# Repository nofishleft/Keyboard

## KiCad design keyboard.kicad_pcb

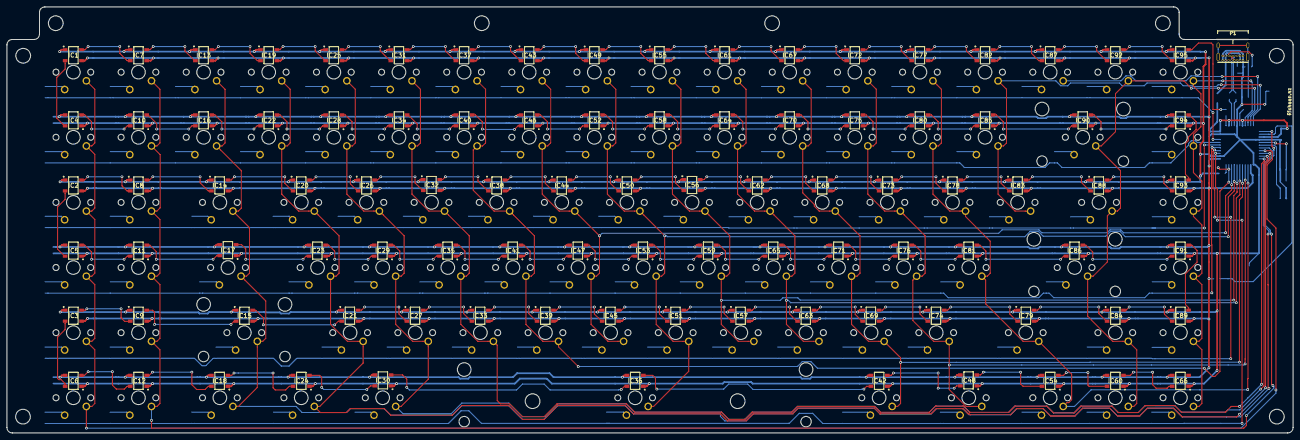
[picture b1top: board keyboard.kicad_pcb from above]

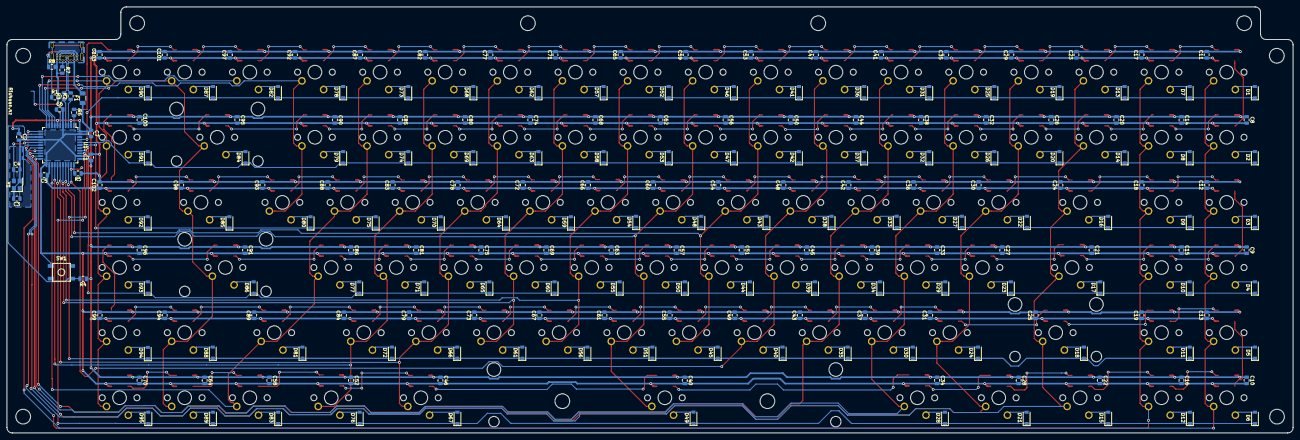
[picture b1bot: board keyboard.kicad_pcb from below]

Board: 2 copper layers, 376.2 x 124.6 mm, 400 parts (209 on the bottom side), 230 nets.

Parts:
C1, C2, C5: 0.1uF; C_0805_2012Metric
C3, C4: 22pF; C_0805_2012Metric
C6: 1uF; C_0805_2012Metric
C7: 10uF; C_0805_2012Metric
C8, C9, C10, C11, C12, C13, C14, C15, C16, C17, C18, C19, C20, C21, C22, C23, C24, C25, C26, C27, C28, C29, C30, C31, C32, C33, C34, C35, C36, C37, C38, C39, C40, C41, C42, C43, C44, C45, C46, C47, C48, C49, C50, C51, C52, C53, C54, C55, C56, C57, C58, C59, C60, C61, C62, C63, C64, C65, C66, C67, C68, C69, C70, C71, C72, C73, C74, C75, C77, C78, C79, C80, C81, C82, C83, C84, C85, C86, C87, C88, C89, C90, C91, C92, C93, C94, C95, C96, C97, C98, C99, C100, C101, C102, C103: 100nF; C_0805_2012Metric
D1, D2, D3, D4, D5, D6, D7, D8, D9, D10, D11, D12, D13, D14, D15, D16, D17, D18, D19, D20, D21, D22, D23, D24, D25, D26, D27, D28, D29, D30, D31, D32, D33, D34, D35, D36, D37, D38, D39, D40, D41, D42, D43, D44, D45, D46, D47, D48, D49, D50, D51, D52, D53, D54, D55, D56, D57, D58, D59, D60, D61, D62, D63, D64, D65, D66, D67, D68, D69, D70, D71, D72, D73, D74, D75, D76, D77, D78, D79, D80, D81, D82, D83, D84, D85, D86, D87, D88, D89, D90, D91, D92, D93, D94, D95: SOD-123; D_SOD-123
F1: 500mA; Fuse_1206_3216Metric
IC1, IC2, IC3, IC4, IC5, IC6, IC7, IC8, IC9, IC10, IC11, IC12, IC13, IC14, IC15, IC16, IC17, IC18, IC19, IC20, IC21, IC22, IC23, IC24, IC25, IC26, IC27, IC28, IC29, IC30, IC31, IC32, IC33, IC34, IC35, IC36, IC37, IC38, IC39, IC40, IC41, IC42, IC43, IC44, IC45, IC46, IC47, IC48, IC49, IC50, IC51, IC52, IC53, IC54, IC55, IC56, IC57, IC58, IC59, IC60, IC61, IC62, IC63, IC64, IC65, IC66, IC67, IC68, IC69, IC70, IC71, IC72, IC73, IC74, IC75, IC76, IC77, IC78, IC79, IC80, IC81, IC82, IC83, IC84, IC85, IC86, IC87, IC88, IC89, IC90, IC91, IC92, IC93, IC94, IC95: WS2812B
MX0-0, MX0-1, MX0-2, MX0-3, MX0-4, MX0-5, MX0-6, MX0-7, MX0-8, MX0-9, MX0-10, MX0-11, MX0-12, MX0-13, MX0-14, MX0-15, MX0-16, MX0-17, MX1-0, MX1-1, MX1-2, MX1-3, MX1-4, MX1-5, MX1-6, MX1-7, MX1-8, MX1-9, MX1-10, MX1-11, MX1-12, MX1-13, MX1-14, MX1-17, MX2-0, MX2-1, MX2-3, MX2-4, MX2-5, MX2-6, MX2-7, MX2-8, MX2-9, MX2-10, MX2-11, MX2-12, MX2-13, MX2-14, MX2-17, MX3-0, MX3-1, MX3-3, MX3-4, MX3-5, MX3-6, MX3-7, MX3-8, MX3-9, MX3-10, MX3-11, MX3-12, MX3-13, MX3-17, MX4-0, MX4-1, MX4-3, MX4-4, MX4-5, MX4-6, MX4-7, MX4-8, MX4-9, MX4-10, MX4-11, MX4-12, MX4-16, MX4-17, MX5-0, MX5-1, MX5-3, MX5-13, MX5-16, MX5-17: MX-NoLED; MXOnly-1U-NoLED
MX1-16: MX-NoLED; MXOnly-2U-NoLED
MX2-2, MX2-16, MX5-2, MX5-4, MX5-12: MX-NoLED; MXOnly-1.5U-NoLED
MX3-2, MX4-13: MX-NoLED; MXOnly-1.75U-NoLED
MX3-16, MX4-2: MX-NoLED; MXOnly-2.25U-NoLED
MX5-8: MX-NoLED; MXOnly-6.25U-NoLED
MX5-11: MX-NoLED; MXOnly-1.25U-NoLED
P1: USB_C_Plug_USB2.0; USB_C_GCT_USB4085
R1: 33k; R_0805_2012Metric
R2, R3: 22; R_0805_2012Metric
R4, R5: 10k; R_0805_2012Metric
R6: 500; R_0805_2012Metric
R7, R8: 5.1k; R_0805_2012Metric
SW1: SW_Push; SKQG-1155865
U1: ATmega32U4-AU; TQFP-44_10x10mm_P0.8mm
Y1: 16MHz; Crystal_SMD_3225-4Pin_3.2x2.5mm

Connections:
+5V: C1.1, C2.1, C5.1, C7.1, C8.1, C9.1, C10.1, C11.1, C12.1, C13.1, C14.1, C15.1, C16.1, C17.1, C18.1, C19.1, C20.1, C21.1, C22.1, C23.1, C24.1, C25.1, C26.1, C27.1, C28.1, C29.1, C30.1, C31.1, C32.1, C33.1, C34.1, C35.1, C36.1, C37.1, C38.1, C39.1, C40.1, C41.1, C42.1, C43.1, C44.1, C45.1, C46.1, C47.1, C48.1, C49.1, C50.1, C51.1, C52.1, C53.1, C54.1, C55.1, C56.1, C57.1, C58.1, C59.1, C60.1, C61.1, C62.1, C63.1, C64.1, C65.1, C66.1, C67.1, C68.1, C69.1, C70.1, C71.1, C72.1, C73.1, C74.1, C75.1, C77.1, C78.1, C79.1, C80.1, C81.1, C82.1, C83.1, C84.1, C85.1, C86.1, C87.1, C88.1, C89.1, C90.1, C91.1, C92.1, C93.1, C94.1, C95.1, C96.1, C97.1, C98.1, C99.1, C100.1, C101.1, C102.1, C103.1, F1.1, IC1.3, IC2.3, IC3.3, IC4.3, IC5.3, IC6.3, IC7.3, IC8.3, IC9.3, IC10.3, IC11.3, IC12.3, IC13.3, IC14.3, IC15.3, IC16.3, IC17.3, IC18.3, IC19.3, IC20.3, IC21.3, IC22.3, IC23.3, IC24.3, IC25.3, IC26.3, IC27.3, IC28.3, IC29.3, IC30.3, IC31.3, IC32.3, IC33.3, IC34.3, IC35.3, IC36.3, IC37.3, IC38.3, IC39.3, IC40.3, IC41.3, IC42.3, IC43.3, IC44.3, IC45.3, IC46.3, IC47.3, IC48.3, IC49.3, IC50.3, IC51.3, IC52.3, IC53.3, IC54.3, IC55.3, IC56.3, IC57.3, IC58.3, IC59.3, IC60.3, IC61.3, IC62.3, IC63.3, IC64.3, IC65.3, IC66.3, IC67.3, IC68.3, IC69.3, IC70.3, IC71.3, IC72.3, IC73.3, IC74.3, IC75.3, IC76.3, IC77.3, IC78.3, IC79.3, IC80.3, IC81.3, IC82.3, IC83.3, IC84.3, IC85.3, IC86.3, IC87.3, IC88.3, IC89.3, IC90.3, IC91.3, IC92.3, IC93.3, IC94.3, IC95.3, R4.1, U1.2, U1.7, U1.14, U1.24, U1.34, U1.44
COL0: MX0-0.1, MX1-0.1, MX2-0.1, MX3-0.1, MX4-0.1, MX5-0.1, U1.19
COL1: MX0-1.1, MX1-1.1, MX2-1.1, MX3-1.1, MX4-1.1, MX5-1.1, U1.12
COL2: MX0-2.1, MX1-2.1, MX2-2.1, MX3-2.1, MX4-2.1, MX5-2.1, U1.18
COL3: MX0-3.1, MX1-3.1, MX2-3.1, MX3-3.1, MX4-3.1, MX5-3.1, U1.20
COL4: MX0-4.1, MX1-4.1, MX2-4.1, MX3-4.1, MX4-4.1, MX5-4.1, U1.21
COL5: MX0-5.1, MX1-5.1, MX2-5.1, MX3-5.1, MX4-5.1, U1.22
COL6: MX0-6.1, MX1-6.1, MX2-6.1, MX3-6.1, MX4-6.1, U1.32
COL7: MX0-7.1, MX1-7.1, MX2-7.1, MX3-7.1, MX4-7.1, U1.31
COL8: MX0-8.1, MX1-8.1, MX2-8.1, MX3-8.1, MX4-8.1, MX5-8.1, U1.30
COL9: MX0-9.1, MX1-9.1, MX2-9.1, MX3-9.1, MX4-9.1, U1.29
COL10: MX0-10.1, MX1-10.1, MX2-10.1, MX3-10.1, MX4-10.1, U1.28
COL11: MX0-11.1, MX1-11.1, MX2-11.1, MX3-11.1, MX4-11.1, MX5-11.1, U1.27
COL12: MX0-12.1, MX1-12.1, MX2-12.1, MX3-12.1, MX4-12.1, MX5-12.1, U1.26
COL13: MX0-13.1, MX1-13.1, MX2-13.1, MX3-13.1, MX4-13.1, MX5-13.1, U1.25
COL14: MX0-14.1, MX1-14.1, MX2-14.1, U1.11
COL15: MX0-15.1, U1.10
COL16: MX0-16.1, MX1-16.1, MX2-16.1, MX3-16.1, MX4-16.1, MX5-16.1, U1.9
COL17: MX0-17.1, MX1-17.1, MX2-17.1, MX3-17.1, MX4-17.1, MX5-17.1, U1.8
D+: P1.A6, P1.B6, R3.2
D-: P1.A7, P1.B7, R2.2
GND: C1.2, C2.2, C3.2, C4.2, C5.2, C6.2, C7.2, C8.2, C9.2, C10.2, C11.2, C12.2, C13.2, C14.2, C15.2, C16.2, C17.2, C18.2, C19.2, C20.2, C21.2, C22.2, C23.2, C24.2, C25.2, C26.2, C27.2, C28.2, C29.2, C30.2, C31.2, C32.2, C33.2, C34.2, C35.2, C36.2, C37.2, C38.2, C39.2, C40.2, C41.2, C42.2, C43.2, C44.2, C45.2, C46.2, C47.2, C48.2, C49.2, C50.2, C51.2, C52.2, C53.2, C54.2, C55.2, C56.2, C57.2, C58.2, C59.2, C60.2, C61.2, C62.2, C63.2, C64.2, C65.2, C66.2, C67.2, C68.2, C69.2, C70.2, C71.2, C72.2, C73.2, C74.2, C75.2, C77.2, C78.2, C79.2, C80.2, C81.2, C82.2, C83.2, C84.2, C85.2, C86.2, C87.2, C88.2, C89.2, C90.2, C91.2, C92.2, C93.2, C94.2, C95.2, C96.2, C97.2, C98.2, C99.2, C100.2, C101.2, C102.2, C103.2, IC1.1, IC2.1, IC3.1, IC4.1, IC5.1, IC6.1, IC7.1, IC8.1, IC9.1, IC10.1, IC11.1, IC12.1, IC13.1, IC14.1, IC15.1, IC16.1, IC17.1, IC18.1, IC19.1, IC20.1, IC21.1, IC22.1, IC23.1, IC24.1, IC25.1, IC26.1, IC27.1, IC28.1, IC29.1, IC30.1, IC31.1, IC32.1, IC33.1, IC34.1, IC35.1, IC36.1, IC37.1, IC38.1, IC39.1, IC40.1, IC41.1, IC42.1, IC43.1, IC44.1, IC45.1, IC46.1, IC47.1, IC48.1, IC49.1, IC50.1, IC51.1, IC52.1, IC53.1, IC54.1, IC55.1, IC56.1, IC57.1, IC58.1, IC59.1, IC60.1, IC61.1, IC62.1, IC63.1, IC64.1, IC65.1, IC66.1, IC67.1, IC68.1, IC69.1, IC70.1, IC71.1, IC72.1, IC73.1, IC74.1, IC75.1, IC76.1, IC77.1, IC78.1, IC79.1, IC80.1, IC81.1, IC82.1, IC83.1, IC84.1, IC85.1, IC86.1, IC87.1, IC88.1, IC89.1, IC90.1, IC91.1, IC92.1, IC93.1, IC94.1, IC95.1, P1.A1, P1.A12, P1.B1, P1.B12, R1.2, R5.1, R7.2, R8.2, SW1.1, U1.5, U1.15, U1.23, U1.35, U1.43, Y1.2, Y1.4
LED_DATA: IC95.4, R6.1
unnamed: C3.1, U1.17, Y1.1
unnamed: C4.1, U1.16, Y1.3
unnamed: C6.1, U1.6
unnamed: D1.2, MX0-0.2
unnamed: D2.2, MX1-0.2
unnamed: D3.2, MX2-0.2
unnamed: D4.2, MX3-0.2
unnamed: D5.2, MX4-0.2
unnamed: D6.2, MX5-0.2
unnamed: D7.2, MX0-1.2
unnamed: D8.2, MX1-1.2
unnamed: D9.2, MX2-1.2
unnamed: D10.2, MX3-1.2
unnamed: D11.2, MX4-1.2
unnamed: D12.2, MX5-1.2
unnamed: D13.2, MX0-2.2
unnamed: D14.2, MX1-2.2
unnamed: D15.2, MX5-2.2
unnamed: D16.2, MX2-2.2
unnamed: D17.2, MX3-2.2
unnamed: D18.2, MX4-2.2
unnamed: D19.2, MX0-3.2
unnamed: D20.2, MX1-3.2
unnamed: D21.2, MX5-3.2
unnamed: D22.2, MX2-3.2
unnamed: D23.2, MX3-3.2
unnamed: D24.2, MX4-3.2
unnamed: D25.2, MX0-4.2
unnamed: D26.2, MX1-4.2
unnamed: D27.2, MX2-4.2
unnamed: D28.2, MX5-4.2
unnamed: D29.2, MX3-4.2
unnamed: D30.2, MX4-4.2
unnamed: D31.2, MX0-5.2
unnamed: D32.2, MX1-5.2
unnamed: D33.2, MX2-5.2
unnamed: D34.2, MX3-5.2
unnamed: D35.2, MX4-5.2
unnamed: D36.2, MX0-6.2
unnamed: D37.2, MX1-6.2
unnamed: D38.2, MX2-6.2
unnamed: D39.2, MX3-6.2
unnamed: D40.2, MX4-6.2
unnamed: D41.2, MX0-7.2
unnamed: D42.2, MX1-7.2
unnamed: D43.2, MX2-7.2
unnamed: D44.2, MX3-7.2
unnamed: D45.2, MX4-7.2
unnamed: D46.2, MX0-8.2
unnamed: D47.2, MX1-8.2
unnamed: D48.2, MX2-8.2
unnamed: D49.2, MX5-8.2
unnamed: D50.2, MX3-8.2
unnamed: D51.2, MX4-8.2
unnamed: D52.2, MX0-9.2
unnamed: D53.2, MX1-9.2
unnamed: D54.2, MX2-9.2
unnamed: D55.2, MX3-9.2
unnamed: D56.2, MX4-9.2
unnamed: D57.2, MX0-10.2
unnamed: D58.2, MX1-10.2
unnamed: D59.2, MX2-10.2
unnamed: D60.2, MX3-10.2
unnamed: D61.2, MX4-10.2
unnamed: D62.2, MX0-11.2
unnamed: D63.2, MX1-11.2
unnamed: D64.2, MX2-11.2
unnamed: D65.2, MX3-11.2
unnamed: D66.2, MX4-11.2
unnamed: D67.2, MX5-11.2
unnamed: D68.2, MX0-12.2
unnamed: D69.2, MX1-12.2
unnamed: D70.2, MX2-12.2
unnamed: D71.2, MX3-12.2
unnamed: D72.2, MX4-12.2
unnamed: D73.2, MX0-13.2
unnamed: D74.2, MX1-13.2
unnamed: D75.2, MX2-13.2
unnamed: D76.2, MX5-12.2
unnamed: D77.2, MX3-13.2
unnamed: D78.2, MX0-14.2
unnamed: D79.2, MX1-14.2
unnamed: D80.2, MX2-14.2
unnamed: D81.2, MX4-13.2
unnamed: D82.2, MX0-15.2
unnamed: D83.2, MX5-13.2
unnamed: D84.2, MX1-16.2
unnamed: D85.2, MX2-16.2
unnamed: D86.2, MX3-16.2
unnamed: D87.2, MX0-16.2
unnamed: D88.2, MX4-16.2
unnamed: D89.2, MX5-16.2
unnamed: D90.2, MX0-17.2
unnamed: D91.2, MX1-17.2
unnamed: D92.2, MX2-17.2
unnamed: D93.2, MX3-17.2
unnamed: D94.2, MX4-17.2
unnamed: D95.2, MX5-17.2
unnamed: IC1.2, IC4.4
unnamed: IC1.4, IC7.2
unnamed: IC2.2, IC5.4
unnamed: IC2.4, IC8.2
unnamed: IC3.2, IC6.4
unnamed: IC3.4, IC9.2
unnamed: IC10.2, IC16.4
unnamed: IC4.2, IC10.4
unnamed: IC11.2, IC17.4
unnamed: IC5.2, IC11.4
unnamed: IC12.2, IC18.4
unnamed: IC6.2, IC12.4
unnamed: IC7.4, IC13.2
unnamed: IC13.4, IC19.2
unnamed: IC8.4, IC14.2
unnamed: IC14.4, IC20.2
unnamed: IC9.4, IC15.2
unnamed: IC15.4, IC21.2
unnamed: IC16.2, IC22.4
unnamed: IC17.2, IC23.4
unnamed: IC18.2, IC24.4
unnamed: IC19.4, IC25.2
unnamed: IC20.4, IC26.2
unnamed: IC21.4, IC27.2
unnamed: IC22.2, IC28.4
unnamed: IC23.2, IC29.4
unnamed: IC24.2, IC30.4
unnamed: IC25.4, IC31.2
unnamed: IC26.4, IC32.2
unnamed: IC27.4, IC33.2
unnamed: IC28.2, IC34.4
unnamed: IC29.2, IC35.4
unnamed: IC30.2, IC36.4
unnamed: IC31.4, IC37.2
unnamed: IC32.4, IC38.2
unnamed: IC33.4, IC39.2
unnamed: IC34.2, IC40.4
unnamed: IC35.2, IC41.4
unnamed: IC36.2, IC42.4
unnamed: IC37.4, IC43.2
unnamed: IC38.4, IC44.2
unnamed: IC39.4, IC45.2
unnamed: IC40.2, IC46.4
unnamed: IC41.2, IC47.4
unnamed: IC42.2, IC48.4
unnamed: IC43.4, IC49.2
unnamed: IC44.4, IC50.2
unnamed: IC45.4, IC51.2
unnamed: IC46.2, IC52.4
unnamed: IC47.2, IC53.4
unnamed: IC48.2, IC54.4
unnamed: IC49.4, IC55.2
unnamed: IC50.4, IC56.2
unnamed: IC51.4, IC57.2
unnamed: IC52.2, IC58.4
unnamed: IC53.2, IC59.4
unnamed: IC54.2, IC60.4
unnamed: IC55.4, IC61.2
unnamed: IC56.4, IC62.2
unnamed: IC57.4, IC63.2
unnamed: IC58.2, IC64.4
unnamed: IC59.2, IC65.4
unnamed: IC60.2, IC66.4
unnamed: IC61.4, IC67.2
unnamed: IC62.4, IC68.2
unnamed: IC63.4, IC69.2
unnamed: IC64.2, IC70.4
unnamed: IC65.2, IC71.4
unnamed: IC67.4, IC72.2
unnamed: IC68.4, IC73.2
unnamed: IC69.4, IC74.2
unnamed: IC70.2, IC75.4
unnamed: IC71.2, IC76.4
unnamed: IC72.4, IC77.2
unnamed: IC73.4, IC78.2
unnamed: IC74.4, IC79.2
unnamed: IC75.2, IC80.4
unnamed: IC76.2, IC81.4
unnamed: IC77.4, IC82.2
unnamed: IC78.4, IC83.2
unnamed: IC79.4, IC84.2
unnamed: IC80.2, IC85.4
unnamed: IC81.2, IC86.4
unnamed: IC82.4, IC87.2
unnamed: IC83.4, IC88.2
unnamed: IC84.4, IC89.2
unnamed: IC85.2, IC90.4
unnamed: IC86.2, IC91.4
unnamed: IC87.4, IC92.2
unnamed: IC88.4, IC93.2
unnamed: IC89.4, IC91.2
unnamed: IC90.2, IC94.4
unnamed: IC92.4, IC95.2
unnamed: IC93.4, IC94.2
unnamed: P1.A5, R7.1
unnamed: P1.B5, R8.1
unnamed: P1.S1, R1.1
unnamed: R2.1, U1.3
unnamed: R3.1, U1.4
unnamed: R4.2, SW1.2, U1.13
unnamed: R5.2, U1.33
unnamed: R6.2, U1.1
ROW0: D1.1, D7.1, D13.1, D19.1, D25.1, D31.1, D36.1, D41.1, D46.1, D52.1, D57.1, D62.1, D68.1, D73.1, D78.1, D82.1, D87.1, D90.1, U1.41
ROW1: D2.1, D8.1, D14.1, D20.1, D26.1, D32.1, D37.1, D42.1, D47.1, D53.1, D58.1, D63.1, D69.1, D74.1, D79.1, D84.1, D91.1, U1.40
ROW2: D3.1, D9.1, D16.1, D22.1, D27.1, D33.1, D38.1, D43.1, D48.1, D54.1, D59.1, D64.1, D70.1, D75.1, D80.1, D85.1, D92.1, U1.39
ROW3: D4.1, D10.1, D17.1, D23.1, D29.1, D34.1, D39.1, D44.1, D50.1, D55.1, D60.1, D65.1, D71.1, D77.1, D86.1, D93.1, U1.38
ROW4: D5.1, D11.1, D18.1, D24.1, D30.1, D35.1, D40.1, D45.1, D51.1, D56.1, D61.1, D66.1, D72.1, D81.1, D88.1, D94.1, U1.37
ROW5: D6.1, D12.1, D15.1, D21.1, D28.1, D49.1, D67.1, D76.1, D83.1, D89.1, D95.1, U1.36
VCC: F1.2, P1.A4, P1.A9, P1.B4, P1.B9

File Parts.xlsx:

No | Part Description | Package | Value | Qty | Ref | Note
1 | Resistor_SMD | R_0805_2012Metric | 5.1k | 2 | R7, R8 |  | https://nz.element14.com/vishay/crcw08055k10fkea/res-5k1-1-0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
2 | Resistor_SMD | R_0805_2012Metric | 500 | 1 | R6 |  | https://nz.element14.com/yageo/rc0805fr-07470rl/res-470r-1-0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
3 | Resistor_SMD | R_0805_2012Metric | 10k | 2 | R4, R5 |  | https://nz.element14.com/vishay/crcw080510k0fkea/res-10k-1-0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 | https://nz.element14.com/panasonic/era6aeb103v/res-10k-0-1-0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 | https://nz.element14.com/walsin/wr08x1002ftl/res-10k-1-150v-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
4 | Resistor_SMD | R_0805_2012Metric | 22 | 2 | R2, R3 |  | https://nz.element14.com/walsin/wr08x22r0ftl/res-22r-1-150v-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 | https://nz.element14.com/yageo/rc0805fr-0722rl/res-22r-1-0-1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
5 | Resistor_SMD | R_0805_2012Metric | 33k | 1 | R1 |  | https://nz.element14.com/vishay/crcw080533k2fkea/res-33k2-1-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
6 | Fuse_SMD | Fuse_1206_3216Metric | 500mA | 1 | F1 |  | https://nz.element14.com/littelfuse/0437-500wr/fuse-0-5a-63v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
7 | MicroProcessor | TQFP-44_10x10mm_P0.8mm | ATmega32U4-AU | 1 | U1 |  | https://www.digikey.co.nz/product-detail/en/microchip-techno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
8 | LED | WS2812B | WS2812B | 95 | IC1-IC95 |  | https://www.aliexpress.com/item/32810203444.html
9 | Capacitor_SMD | C_0805_2012Metric | 0.1uF | 3 | C1, C2, C5 |  | https://nz.element14.com/avx/08051c104jat2a/cap-0-1-f-100v-5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
10 | Capacitor_SMD | C_0805_2012Metric | 22pF | 2 | C3, C4 |  | https://nz.element14.com/avx/08055a200jat2a/cap-20pf-50v-5-c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
11 | Capacitor_SMD | C_0805_2012Metric | 1uF | 1 | C6 |  | https://nz.element14.com/avx/08053c105k4z2a/cap-1-f-25v-10-x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
12 | Capacitor_SMD | C_0805_2012Metric | 10uF | 1 | C7 |  | https://nz.element14.com/avx/08053d106kat2a/cap-10-f-25v-10-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
13 | Capacitor_SMD | C_0805_2012Metric | 100nF | 95 | C8-C103 |  | Same as 0.1uF
14 | Diode_SMD | D_SOD-123 | D_SOD-123 | 95 | D1-D95 |  | https://nz.element14.com/diodes-inc/1n4148w-7-f/diode-switch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
15 | Crystal_SMD | Crystal_SMD_3225-4Pin_3.2x2.5mm | 16MHz | 1 | Y1 |  | https://nz.element14.com/epson/x1e0000210120-tsx-3225-16mhz-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
16 | Push Button | SKQG-1155865 | SW_Push | 1 | SW1 |  | https://nz.element14.com/alcoswitch-te-connectivity/fsm1lpat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
17 | USB Type C | USB4085-GF-A |  | 1 | P1 |  | https://www.digikey.com/product-detail/en/gct/USB4085-GF-A/2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
 |  |  |  |  |  | Wick | https://www.digikey.co.nz/product-detail/en/menda-easybraid/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
 |  |  |  |  |  | Flux Pen | https://www.digikey.com/products/en?mpart=760089&v=82
 |  |  |  |  |  |  | https://www.digikey.com/products/en?mpart=83-1000-0186&v=117
 |  |  |  |  |  | Flux Paste | https://www.digikey.com/product-detail/en/mg-chemicals/8341-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

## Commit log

2019-09-26 Initialize Project
2019-09-26 Add Submodules
2019-09-26 Add symbol & footprint libraries
2019-09-27 Initial Schematic Setup
2019-09-27 Intended Final Layout Design
2019-09-27 Key Matrix
2019-09-27 Schematic & Footprint bindings
2019-09-29 Routing & LEDS
2019-09-29 Track Routing Cleaning
2019-09-30 Track Routine Cleaning
2019-09-30 Ground Fill, Track Clearances, USB C CC & VCONN
2019-09-30 Edge Cut, Mounting Holes, Silk Screen
2019-09-30 Mounting Holes, Hide Mounting Hole Silk Screen
2019-10-01 Production
2019-10-02 .Hex firmware file
    Can be flashed using QMK Toolbox
